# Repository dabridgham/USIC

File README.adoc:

= USIC - Unibus Storage and I/O Card

The USIC is a Unibus card with an FPGA and SD cards that emulates the old DEC disk
controllers and drives.

This repository is the KiCad project for the hardware, the USIC board
itself.  In addition there are separate projects for a QBUS version of
the board, the http://github.com/dabridgham/QSIC[QSIC], the
http://github.com/dabridgham/QSIC-Verilog[Verilog code] that runs on
the FPGAs, and the code that runs on the embedded soft processor (not
yet started).

A companion http://github.com/dabridgham/Indicator-Panel[indicator
panel] is also available for those who want the blinkenlights.

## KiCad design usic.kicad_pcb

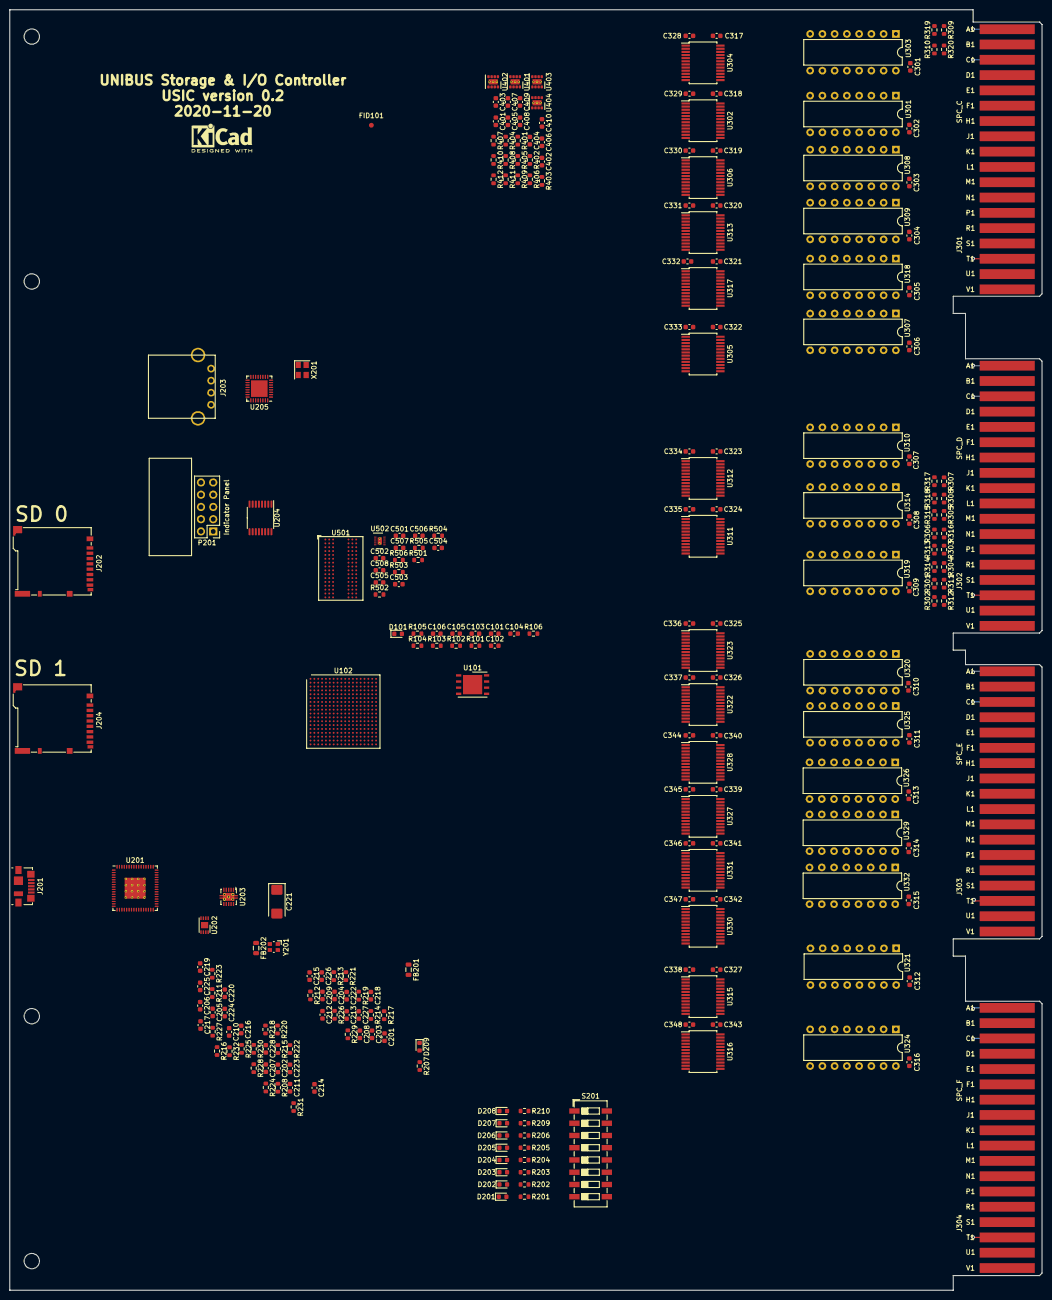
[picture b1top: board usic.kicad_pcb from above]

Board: 6 copper layers, 214.1 x 265.6 mm, 253 parts (0 on the bottom side), 359 nets.

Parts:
C101, C102, C103, C104, C106, C218, C226, C401, C405, C407, C409, C501, C502: 22µF 10V; C_0603_1608Metric
C105, C201, C202, C203, C204, C205, C206, C207, C209, C211, C212, C214, C217, C219, C220, C222, C223, C227, C301, C302, C303, C304, C305, C306, C307, C308, C309, C310, C311, C312, C313, C314, C315, C316, C317, C318, C319, C320, C321, C322, C323, C324, C325, C326, C327, C328, C329, C330, C331, C332, C333, C334, C335, C336, C337, C338, C339, C340, C341, C342, C343, C344, C345, C346, C347, C348, C508: 100nF; C_0603_1608Metric
C208, C210: 4.7µF 6.3V; C_0603_1608Metric
C213: 3.3µF 6.3V; C_0603_1608Metric
C215, C216: 8pF; C_0603_1608Metric
C221: 150µF; CP_EIA-6032-28_Kemet-C
C224, C225: 1µF; C_0603_1608Metric
C228: 10nF; C_0603_1608Metric
C402, C403, C404, C406, C408, C410, C503, C504, C505, C506: 10µF 10V; C_0603_1608Metric
C507: 220nF; C_0603_1608Metric
D101, D201, D202, D203, D204, D205, D206, D207, D208, D209: green; LED_0603_1608Metric
FB201, FB202: Ferrite_Bead_Small; L_0805_2012Metric
FID101: Fiducial; Fiducial_1mm_Mask2mm
Handle_101, Handle_102: Handle; DEC-Handle
Handle_Hole_101, Handle_Hole_102, Handle_Hole_103, Handle_Hole_104: MountingHole; mounting hole .125
J201: USB_B_Micro; USB_Micro-B_Molex_47346-0001
J202: SD 0; microSD_HC_Hirose_DM3BT-DSF-PEJS
J203: USB_A; USB-A-Amphenol-UE27
J204: SD 1; microSD_HC_Hirose_DM3BT-DSF-PEJS
J301: SPC_C; DEC_Edge_Fingers_single_height
J302: SPC_D; DEC_Edge_Fingers_single_height
J303: SPC_E; DEC_Edge_Fingers_single_height
J304: SPC_F; DEC_Edge_Fingers_single_height
LOGO101: KiCad Logo; KiCad-Logo2_5mm_SilkScreen
P201: Indicator Panel; Box_Header_2x05_P2.54mm
R101, R102, R105, R106: 4.7k; R_0603_1608Metric
R103: 2.4k; R_0603_1608Metric
R104, R201, R202, R203, R204, R205, R206, R209, R210, R214, R501: 240; R_0603_1608Metric
R207: 1k; R_0603_1608Metric
R208: 12k 1%; R_0603_1608Metric
R211, R212, R213, R504, R505, R506: 10k; R_0603_1608Metric
R215: 2.2k; R_0603_1608Metric
R216, R217: 100k; R_0603_1608Metric
R218, R226: 4.7; R_0603_1608Metric
R219, R220, R221, R222, R223, R227, R228, R229, R230, R231: 50k; R_0603_1608Metric
R224: 56.2k; R_0603_1608Metric
R225: 20k; R_0603_1608Metric
R232: 8.06k; R_0603_1608Metric
R301, R302, R303, R304, R305, R306, R307, R308, R309, R310: 330; R_0603_1608Metric
R311, R312, R313, R314, R315, R316, R317, R318, R319, R320: 680; R_0603_1608Metric
R401: 499k; R_0603_1608Metric
R402: 511k; R_0603_1608Metric
R403: 162k; R_0603_1608Metric
R404, R407, R410: 499k 1%; R_0603_1608Metric
R405: 200k 1%; R_0603_1608Metric
R406, R409, R412: 162k 1%; R_0603_1608Metric
R408: 143k 1%; R_0603_1608Metric
R411: 40.2 1%; R_0603_1608Metric
R502: 89 1%; R_0603_1608Metric
R503: 47k; R_0603_1608Metric
S201: Config; SW_DIP_SPSTx08_Slide_6.7x21.88mm_W6.73mm_P2.54mm_LowProfile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
U101: MT25Q-so8; DFN-8-1EP_6x5mm_P1.27mm_EP4x4mm
U102: XC7A75T-CSG324; Xilinx_CSG324
U201: FT2232HQ; QFN-64-1EP_9x9mm_P0.5mm_EP4.35x4.35mm_ThermalVias
U202: 93CxxC; DFN-8-1EP_3x2mm_P0.5mm_EP1.3x1.5mm
U203: TPS2561; VSON-10-1EP_3x3mm_P0.5mm_EP1.65x2.4mm_ThermalVias
U204: MAX3033E; TSSOP-16_4.4x5mm_P0.65mm
U205: USB3340; QFN-32-1EP_5x5mm_P0.5mm_EP3.45x3.45mm
U301, U303, U307, U308, U309, U310, U314, U318, U319, U320, U321, U324, U325, U326, U329, U332: DS8641-LR; DIP-16_W7.62mm
U302, U304, U305, U306, U311, U312, U313, U315, U316, U317, U322, U323, U327, U328, U330, U331: 74LVC7T245; SSOP-24_5.3x8.2mm_P0.65mm
U401, U402, U403, U404: TPS82085; Texas_SIL0008D_MicroSiP-8-1EP_2.8x3mm_P0.65mm_EP1.1x1.9mm_T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
U501: IS43TR16128B; BGA-96_9.0x13.0mm_Layout2x3x16_P0.8mm
U502: TPS51206; WSON-10-1EP_2x2mm_P0.4mm_EP0.9x1.5mm_ThermalVias
X201: ASE-24.000MHz; Oscillator_SMD_Abracon_ASE-4Pin_3.2x2.5mm
Y201: 12 MHz; Crystal_SMD_Abracon_ABM10-4Pin_2.5x2.0mm

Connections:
/1V0: C404.1, C409.1, R410.1, R411.1, U102.F8 (VCCINT), U102.F10 (VCCBRAM), U102.G7 (VCCINT), U102.G9 (VCCINT), U102.G11 (VCCBRAM), U102.H8 (VCCINT), U102.J7 (VCCINT), U102.J11 (VCCINT), U102.K8 (VCCINT), U102.L7 (VCCINT), U102.L11 (VCCINT), U102.M8 (VCCINT), U102.M10 (VCCINT), U102.N7 (VCCINT), U102.N9 (VCCINT), U102.N11 (VCCINT), U404.8 (Vout)
/1V5: C407.1, C501.1, C502.1, C503.1, C504.1, R407.1, R408.1, U102.A7 (VCCO_35), U102.C3 (VCCO_35), U102.D6 (VCCO_35), U102.F2 (VCCO_35), U102.G5 (VCCO_35), U102.J1 (VCCO_35), U403.8 (Vout), U501.A1 (VDDQ1), U501.A8 (VDDQ2), U501.B2 (VDD1), U501.C1 (VDDQ3), U501.C9 (VDDQ4), U501.D2 (VDDQ5), U501.D9 (VDD2), U501.E9 (VDDQ6), U501.F1 (VDDQ7), U501.G7 (VDD3), U501.H2 (VDDQ8), U501.H9 (VDDQ9), U501.K2 (VDD4), U501.K8 (VDD5), U501.N1 (VDD6), U501.N9 (VDD7), U501.R1 (VDD8), U501.R9 (VDD9), U502.1 (VDDQSNS)
/1V8: C403.1, C405.1, R404.1, R405.1, U102.F12 (VCCAUX), U102.H10 (VCCADC_0), U102.H12 (VCCAUX), U102.K12 (VCCAUX), U102.M12 (VCCAUX), U402.8 (Vout)
/3V3: C101.1, C102.2, C103.1, C104.2, C105.2, C106.2, C203.1, C205.1, C206.1, C211.1, C212.1, C214.2, C220.2, C222.1, C223.1, C228.1, C328.1, C329.1, C330.1, C331.1, C332.1, C333.1, C334.1, C335.1, C336.1, C337.1, C338.1, C344.1, C345.1, C346.1, C347.1, C348.1, C401.1, C505.1, C508.1, D209.2 (A), FB201.2, FB202.2, R101.1, R102.1, R103.1, R104.1, R105.1, R106.1, R201.1, R202.1, R203.1, R204.1, R205.1, R206.1, R207.2, R209.1, R210.1, R211.1, R212.1, R213.1, R218.2, R219.1, R220.1, R221.1, R222.1, R223.1, R226.2, R227.1, R228.1, R229.1, R230.1, R231.1, R401.1, R402.1, R505.2, R506.2, U101.8 (Vcc), U102.A17 (VCCO_15), U102.B10 (VCCO_16), U102.C13 (VCCO_15), U102.D16 (VCCO_15), U102.G15 (VCCO_15), U102.H18 (VCCO_15), U102.K4 (VCCO_34), U102.K14 (VCCO_15), U102.L17 (VCCO_14), U102.N3 (VCCO_34), U102.N13 (VCCO_14), U102.P6 (VCCO_34), U102.P8 (CFGBVS_0), U102.P12 (M0_0), U102.P16 (VCCO_14), U102.T2 (VCCO_34), U102.T12 (VCCO_14), U102.U5 (VCCO_34), U102.U15 (VCCO_14), U102.V8 (VCCO_34), U102.V18 (VCCO_14), U201.20 (VCCIO), U201.31 (VCCIO), U201.42 (VCCIO), U201.50 (VREGIN), U201.56 (VCCIO), U202.6 (ORG), U202.8 (VCC), U204.4 (EN12), U204.12 (EN34), U204.16 (VDD), U205.8 (REFSEL[0]), U205.11 (REFSEL[1]), U205.14 (REFSEL[2]), U205.21 (VBAT), U205.32 (VDDIO), U302.1 (VCCa), U302.2 (A->B), U304.1 (VCCa), U304.2 (A->B), U305.1 (VCCa), U306.1 (VCCa), U311.1 (VCCa), U311.2 (A->B), U312.1 (VCCa), U313.1 (VCCa), U313.2 (A->B), U315.1 (VCCa), U315.2 (A->B), U316.1 (VCCa), U317.1 (VCCa), U322.1 (VCCa), U322.2 (A->B), U323.1 (VCCa), U327.1 (VCCa), U327.2 (A->B), U328.1 (VCCa), U330.1 (VCCa), U330.2 (A->B), U331.1 (VCCa), U401.8 (Vout), U502.2 (VLDOIN), U502.10 (VDD), X201.4 (Vdd)
/5V0: C217.1, C301.1, C302.1, C303.1, C304.1, C305.1, C306.1, C307.1, C308.1, C309.1, C310.1, C311.1, C312.1, C313.1, C314.1, C315.1, C316.1, C317.1, C318.1, C319.1, C320.1, C321.1, C322.1, C323.1, C324.1, C325.1, C326.1, C327.1, C339.1, C340.1, C341.1, C342.1, C343.1, C402.1, C406.1, C408.1, C410.1, J301.A2 (+5V), J302.A2 (+5V), J303.A2 (+5V), J304.A2 (+5V), R216.1, R217.1, R301.1, R302.1, R303.1, R304.1, R305.1, R306.1, R307.1, R308.1, R309.1, R310.1, U203.2 (IN), U203.3 (IN), U301.16 (VCC), U302.23 (VCCb), U302.24 (VCCb), U303.16 (VCC), U304.23 (VCCb), U304.24 (VCCb), U305.23 (VCCb), U305.24 (VCCb), U306.23 (VCCb), U306.24 (VCCb), U307.16 (VCC), U308.16 (VCC), U309.16 (VCC), U310.16 (VCC), U311.23 (VCCb), U311.24 (VCCb), U312.23 (VCCb), U312.24 (VCCb), U313.23 (VCCb), U313.24 (VCCb), U314.16 (VCC), U315.23 (VCCb), U315.24 (VCCb), U316.23 (VCCb), U316.24 (VCCb), U317.23 (VCCb), U317.24 (VCCb), U318.16 (VCC), U319.16 (VCC), U320.16 (VCC), U321.16 (VCC), U322.23 (VCCb), U322.24 (VCCb), U323.23 (VCCb), U323.24 (VCCb), U324.16 (VCC), U325.16 (VCC), U326.16 (VCC), U327.23 (VCCb), U327.24 (VCCb), U328.23 (VCCb), U328.24 (VCCb), U329.16 (VCC), U330.23 (VCCb), U330.24 (VCCb), U331.23 (VCCb), U331.24 (VCCb), U332.16 (VCC), U401.1 (En), U401.3 (Vin), U401.4 (Vin), U402.1 (En), U402.3 (Vin), U402.4 (Vin), U403.1 (En), U403.3 (Vin), U403.4 (Vin), U404.1 (En), U404.3 (Vin), U404.4 (Vin)
/CLK_INPUT: U102.D15 (IO_L12P_T1_MRCC_15), U102.H16 (IO_L13P_T2_MRCC_15), U102.N5 (IO_L13P_T2_MRCC_34), U102.P15 (IO_L13P_T2_MRCC_14), U102.P17 (IO_L12P_T1_MRCC_14), U102.T5 (IO_L12P_T1_MRCC_34)
/I/O/D+: J201.3 (D+), U201.8 (D+)
/I/O/D-: J201.2 (D-), U201.7 (D-)
/I/O/IPblank_N: P201.7, U204.5 (O2-)
/I/O/IPblank_P: P201.6, U204.6 (O2+)
/I/O/IPclk_N: P201.10, U204.3 (O1-)
/I/O/IPclk_P: P201.9, U204.2 (O1+)
/I/O/IPdata_N: P201.2, U204.13 (O4-)
/I/O/IPdata_P: P201.1, U204.14 (O4+)
/I/O/IPlatch_N: P201.5, U204.11 (O3-)
/I/O/IPlatch_P: P201.4, U204.10 (O3+)
/LED_0: D201.1 (K), U102.V9 (IO_L21N_T3_DQS_34)
/LED_1: D202.1 (K), U102.U7 (IO_L22P_T3_34)
/LED_2: D203.1 (K), U102.U6 (IO_L22N_T3_34)
/LED_3: D204.1 (K), U102.R7 (IO_L23P_T3_34)
/LED_4: D205.1 (K), U102.T6 (IO_L23N_T3_34)
/LED_5: D206.1 (K), U102.R8 (IO_L24P_T3_34)
/LED_6: D207.1 (K), U102.T8 (IO_L24N_T3_34)
/LED_7: D208.1 (K), U102.U8 (IO_25_34)
/Memory/A0: U102.C5 (IO_L1N_T0_AD4N_35), U501.N3 (A0)
/Memory/A1: U102.B6 (IO_L2N_T0_AD12N_35), U501.P7 (A1)
/Memory/A2: U102.C7 (IO_L4N_T0_35), U501.P3 (A2)
/Memory/A3: U102.D5 (IO_L11P_T1_SRCC_35), U501.N2 (A3)
/Memory/A4: U102.A3 (IO_L8N_T1_AD14N_35), U501.P8 (A4)
/Memory/A5: U102.E7 (IO_L6P_T0_35), U501.P2 (A5)
/Memory/A6: U102.A4 (IO_L8P_T1_AD14P_35), U501.R8 (A6)
/Memory/A7: U102.C6 (IO_L1P_T0_AD4P_35), U501.R2 (A7)
/Memory/A8: U102.A6 (IO_L3P_T0_DQS_AD5P_35), U501.T8 (A8)
/Memory/A9: U102.D8 (IO_L4P_T0_35), U501.R3 (A9)
/Memory/A10: U102.B2 (IO_L10N_T1_AD15N_35), U501.L7 (A10/AP)
/Memory/A11: U102.A5 (IO_L3N_T0_DQS_AD5N_35), U501.R7 (A11)
/Memory/A12: U102.B3 (IO_L10P_T1_AD15P_35), U501.N7 (A12/BC#)
/Memory/A13: U102.B7 (IO_L2P_T0_AD12P_35), U501.T3 (A13)
/Memory/BA0: U102.E5 (IO_L5N_T0_AD13N_35), U501.M2 (BA0)
/Memory/BA1: U102.A1 (IO_L9N_T1_DQS_AD7N_35), U501.N8 (BA1)
/Memory/BA2: U102.E6 (IO_L5P_T0_AD13P_35), U501.M3 (BA2)
/Memory/CAS#: U102.D3 (IO_L12N_T1_MRCC_35), U501.K3 (CAS#)
/Memory/CK: R502.2, U102.C4 (IO_L7P_T1_AD6P_35), U501.J7 (CK)
/Memory/CK#: R502.1, U102.B4 (IO_L7N_T1_AD6N_35), U501.K7 (CK#)
/Memory/CKE: U102.B1 (IO_L9P_T1_DQS_AD7P_35), U501.K9 (CKE)
/Memory/DML: U102.G1 (IO_L17N_T2_35), U501.E7 (DML)
/Memory/DMU: U102.G6 (IO_L19P_T3_35), U501.D3 (DMU)
/Memory/DQL0: U102.H1 (IO_L17P_T2_35), U501.E3 (DQL0)
/Memory/DQL1: U102.F1 (IO_L18P_T2_35), U501.F7 (DQL1)
/Memory/DQL2: U102.E2 (IO_L14P_T2_SRCC_35), U501.F2 (DQL2)
/Memory/DQL3: U102.E1 (IO_L18N_T2_35), U501.F8 (DQL3)
/Memory/DQL4: U102.F4 (IO_L13P_T2_MRCC_35), U501.H3 (DQL4)
/Memory/DQL5: U102.C1 (IO_L16N_T2_35), U501.H8 (DQL5)
/Memory/DQL6: U102.F3 (IO_L13N_T2_MRCC_35), U501.G2 (DQL6)
/Memory/DQL7: U102.D2 (IO_L14N_T2_SRCC_35), U501.H7 (DQL7)
/Memory/DQSL: U102.H2 (IO_L15P_T2_DQS_35), U501.F3 (DQSL)
/Memory/DQSL#: U102.G2 (IO_L15N_T2_DQS_35), U501.G3 (DQSL#)
/Memory/DQSU: U102.J4 (IO_L21P_T3_DQS_35), U501.C7 (DQSU)
/Memory/DQSU#: U102.H4 (IO_L21N_T3_DQS_35), U501.B7 (DQSU#)
/Memory/DQU0: U102.G4 (IO_L20P_T3_35), U501.D7 (DQU0)
/Memory/DQU1: U102.H5 (IO_L24N_T3_35), U501.C3 (DQU1)
/Memory/DQU2: U102.G3 (IO_L20N_T3_35), U501.C8 (DQU2)
/Memory/DQU3: U102.H6 (IO_L24P_T3_35), U501.C2 (DQU3)
/Memory/DQU4: U102.J2 (IO_L22N_T3_35), U501.A7 (DQU4)
/Memory/DQU5: U102.J3 (IO_L22P_T3_35), U501.A2 (DQU5)
/Memory/DQU6: U102.K1 (IO_L23N_T3_35), U501.B8 (DQU6)
/Memory/DQU7: U102.K2 (IO_L23P_T3_35), U501.A3 (DQU7)
/Memory/ODT: U102.F5 (IO_0_35), U501.K1 (ODT)
/Memory/RAS#: U102.E3 (IO_L12P_T1_MRCC_35), U501.J3 (RAS#)
/Memory/RESET#: R503.1, U102.J5 (IO_25_35), U501.T2 (RESET#)
/Memory/VREF15: C507.1, U102.D7 (IO_L6N_T0_VREF_35), U102.F6 (IO_L19N_T3_VREF_35), U501.H1 (VREFDQ), U501.M8 (VREFCA), U502.6 (VTTREF)
/Memory/WE#: U102.D4 (IO_L11N_T1_SRCC_35), U501.L3 (WE#)
/PROG_B: R106.2, U102.P9 (PROGRAM_B_0)
/RXD: U102.B9 (IO_L11N_T1_SRCC_16), U201.39 (BDBUS1)
/SW_0: S201.8, U102.U1 (IO_L7P_T1_34)
/SW_1: S201.7, U102.V1 (IO_L7N_T1_34)
/SW_2: S201.6, U102.U4 (IO_L8P_T1_34)
/SW_3: S201.5, U102.U3 (IO_L8N_T1_34)
/SW_4: S201.4, U102.U2 (IO_L9P_T1_DQS_34)
/SW_5: S201.3, U102.V2 (IO_L9N_T1_DQS_34)
/SW_6: S201.2, U102.V5 (IO_L10P_T1_34)
/SW_7: S201.1, U102.V4 (IO_L10N_T1_34)
/TCK: U102.E10 (TCK_0), U201.16 (ADBUS0)
/TDI: U102.E11 (TDI_0), U201.17 (ADBUS1)
/TDO: U102.E13 (TDO_0), U201.18 (ADBUS2)
/TMS: U102.E12 (TMS_0), U201.19 (ADBUS3)
/TXD: U102.C9 (IO_L11P_T1_SRCC_16), U201.38 (BDBUS0)
/Unibus/A0: J303.H2 (A00), U325.1 (bus3)
/Unibus/A1: J303.H1 (A01), U325.15 (bus1)
/Unibus/A2: J303.F1 (A02), U325.12 (bus2)
/Unibus/A3: J303.V2 (A03), U332.15 (bus1)
/Unibus/A4: J303.U2 (A04), U332.1 (bus3)
/Unibus/A5: J303.V1 (A05), U332.12 (bus2)
/Unibus/A6: J303.U1 (A06), U332.4 (bus4)
/Unibus/A7: J303.P2 (A07), U329.1 (bus3)
/Unibus/A8: J303.N2 (A08), U329.4 (bus4)
/Unibus/A9: J303.R1 (A09), U329.15 (bus1)
/Unibus/A10: J303.P1 (A10), U329.12 (bus2)
/Unibus/A11: J303.L1 (A11), U326.15 (bus1)
/Unibus/A12: J303.C1 (A12), U320.1 (bus3)
/Unibus/A13: J303.K2 (A13), U326.1 (bus3)
/Unibus/A14: J303.K1 (A14), U326.4 (bus4)
/Unibus/A15: J303.D2 (A15), U320.12 (bus2)
/Unibus/A16: J303.E2 (A16), U320.4 (bus4)
/Unibus/A17: J303.D1 (A17), U320.15 (bus1)
/Unibus/AC_LO: J301.V1 (AC_LO), U305.8 (A5), U307.1 (bus3)
/Unibus/BBSY: J304.D1 (BBSY), U324.1 (bus3)
/Unibus/BG4_in: J302.S2 (BG4_in), R301.2, R311.1, U312.9 (A6), U319.15 (bus1)
/Unibus/BG4_out: J302.T2 (BG4_out), R302.2, R312.1, U311.8 (A5), U319.12 (bus2)
/Unibus/BG5_in: J302.P2 (BG5_in), R303.2, R313.1, U312.10 (A7), U319.4 (bus4)
/Unibus/BG5_out: J302.R2 (BG5_out), R304.2, R314.1, U311.9 (A6), U319.1 (bus3)
/Unibus/BG6_in: J302.M2 (BG6_in), R305.2, R315.1, U312.8 (A5), U314.15 (bus1)
/Unibus/BG6_out: J302.N2 (BG6_out), R306.2, R316.1, U311.6 (A3), U314.12 (bus2)
/Unibus/BG7_in: J302.K2 (BG7_in), R307.2, R317.1, U310.12 (bus2), U312.6 (A3)
/Unibus/BG7_out: J302.L2 (BG7_out), R308.2, R318.1, U311.7 (A4), U314.1 (bus3)
/Unibus/BR4: J302.H2 (BR4), U310.15 (bus1)
/Unibus/BR5: J302.F2 (BR5), U310.1 (bus3)
/Unibus/BR6: J302.E2 (BR6), U310.4 (bus4)
/Unibus/BR7: J302.D2 (BR7), U307.12 (bus2)
/Unibus/C0: J303.J2 (C0), U321.4 (bus4)
/Unibus/C1: J303.F2 (C1), U321.1 (bus3)
/Unibus/D0: J301.S2 (D00), U318.15 (bus1)
/Unibus/D1: J301.R2 (D01), U309.4 (bus4)
/Unibus/D2: J301.U2 (D02), U318.1 (bus3)
/Unibus/D3: J301.T2 (D03), U318.12 (bus2)
/Unibus/D4: J301.N2 (D04), U309.12 (bus2)
/Unibus/D5: J301.P2 (D05), U309.1 (bus3)
/Unibus/D6: J301.V2 (D06), U318.4 (bus4)
/Unibus/D7: J301.M2 (D07), U309.15 (bus1)
/Unibus/D8: J301.L2 (D08), U308.4 (bus4)
/Unibus/D9: J301.K2 (D09), U308.1 (bus3)
/Unibus/D10: J301.J2 (D10), U308.12 (bus2)
/Unibus/D11: J301.H1 (D11), U308.15 (bus1)
/Unibus/D12: J301.H2 (D12), U301.4 (bus4)
/Unibus/D13: J301.F2 (D13), U301.1 (bus3)
/Unibus/D14: J301.E2 (D14), U301.12 (bus2)
/Unibus/D15: J301.D2 (D15), U301.15 (bus1)
/Unibus/DC_LO: J301.N1 (DC_LO), U305.7 (A4), U307.4 (bus4)
/Unibus/INIT: J302.L1 (INIT), U314.4 (bus4)
/Unibus/INTR: J304.M1 (INTR), U324.15 (bus1)
/Unibus/MSYN: J303.E1 (MSYN), U321.15 (bus1)
/Unibus/NPG_in: J301.A1 (NPG_in), R309.2, R319.1, U303.1 (bus3), U305.4 (A1)
/Unibus/NPG_out: J301.B1 (NPG_out), R310.2, R320.1, U303.4 (bus4), U304.3 (A0)
/Unibus/NPR: J304.J1 (NPR), U324.4 (bus4)
/Unibus/PA: J301.C1 (PA), U303.15 (bus1)
/Unibus/PB: J301.S1 (PB), U307.15 (bus1)
/Unibus/SACK: J304.T2 (SACK), U324.12 (bus2)
/Unibus/SSYN: J303.J1 (SSYN), U321.12 (bus2)
/Unibus/~RxA: U323.22 (~OE), U328.22 (~OE), U331.22 (~OE)
/Unibus/~RxD: U306.22 (~OE), U317.22 (~OE)
/Unibus/~TxA_5: U311.14 (B7), U320.7 (disB), U325.7 (disB), U326.7 (disB), U329.7 (disB), U332.7 (disB)
/Unibus/~TxD_5: U301.7 (disB), U304.14 (B7), U308.7 (disB), U309.7 (disB), U318.7 (disB)
/ip_blank: U102.V7 (IO_L20P_T3_34), U204.7 (I2)
/ip_clk: U102.R5 (IO_L19N_T3_VREF_34), U204.1 (I1)
/ip_data: U102.U9 (IO_L21P_T3_DQS_34), U204.15 (I4)
/ip_latch: U102.V6 (IO_L20N_T3_34), U204.9 (I3)
/sd0_clk: J202.5 (CLK), U102.P2 (IO_L15P_T2_DQS_34)
/sd0_cmd: J202.3 (CMD), R221.2, U102.P3 (IO_L14N_T2_SRCC_34)
/sd0_dat0: J202.7 (DAT0), R220.2, U102.R3 (IO_L11P_T1_SRCC_34)
/sd0_dat1: J202.8 (DAT1), R219.2, U102.T3 (IO_L11N_T1_SRCC_34)
/sd0_dat2: J202.1 (DAT2), R223.2, U102.P5 (IO_L13N_T2_MRCC_34)
/sd0_dat3: J202.2 (DAT3/CD), R222.2, U102.P4 (IO_L14P_T2_SRCC_34)
/sd0_det: J202.9 (DET_B), U102.R2 (IO_L15N_T2_DQS_34)
/sd1_clk: J204.5 (CLK), U102.N6 (IO_L18N_T2_34)
/sd1_cmd: J204.3 (CMD), R229.2, U102.M6 (IO_L18P_T2_34)
/sd1_dat0: J204.7 (DAT0), R228.2, U102.M4 (IO_L16P_T2_34)
/sd1_dat1: J204.8 (DAT1), R227.2, U102.N4 (IO_L16N_T2_34)
/sd1_dat2: J204.1 (DAT2), R231.2, U102.R1 (IO_L17P_T2_34)
/sd1_dat3: J204.2 (DAT3/CD), R230.2, U102.T1 (IO_L17N_T2_34)
/sd1_det: J204.9 (DET_B), U102.R6 (IO_L19P_T3_34)
/usb0_clk60: U102.L6 (IO_L6P_T0_34), U205.1 (CLKOUT)
/usb0_d0: U102.K6 (IO_0_34), U205.3 (DATA0)
/usb0_d1: U102.L1 (IO_L1P_T0_34), U205.4 (DATA1)
/usb0_d2: U102.M1 (IO_L1N_T0_34), U205.5 (DATA2)
/usb0_d3: U102.K3 (IO_L2P_T0_34), U205.6 (DATA3)
/usb0_d4: U102.L3 (IO_L2N_T0_34), U205.7 (DATA4)
/usb0_d5: U102.N2 (IO_L3P_T0_DQS_34), U205.9 (DATA5)
/usb0_d6: U102.N1 (IO_L3N_T0_DQS_34), U205.10 (DATA6)
/usb0_d7: U102.M3 (IO_L4P_T0_34), U205.13 (DATA7)
/usb0_dir: U102.K5 (IO_L5P_T0_34), U205.31 (DIR)
/usb0_nxt: U102.M2 (IO_L4N_T0_34), U205.2 (NXT)
/usb0_reset: U102.L5 (IO_L6N_T0_VREF_34), U205.27 (RESET)
/usp0_stp: U102.L4 (IO_L5N_T0_34), U205.29 (STP)
/~CTS: U102.A8 (IO_L12N_T1_MRCC_16), U201.41 (BDBUS3)
/~DCD: U102.A10 (IO_L14P_T2_SRCC_16), U201.45 (BDBUS6)
/~DSR: U102.C10 (IO_L13N_T2_MRCC_16), U201.44 (BDBUS5)
/~DTR: U102.C11 (IO_L13P_T2_MRCC_16), U201.43 (BDBUS4)
/~RI: U102.D10 (IO_L19N_T3_VREF_16), U201.46 (BDBUS7)
/~RTS: U102.D9 (IO_L6N_T0_VREF_16), U201.40 (BDBUS2)
GND: C101.2, C102.1, C103.2, C104.1, C105.1, C106.1, C201.2, C202.2, C203.2, C204.2, C205.2, C206.2, C207.2, C208.2, C209.2, C210.2, C211.2, C212.2, C213.2, C214.1, C215.1, C216.1, C217.2, C218.2, C219.2, C220.1, C221.2, C222.2, C223.2, C224.2, C225.2, C226.2, C227.2, C228.2, C301.2, C302.2, C303.2, C304.2, C305.2, C306.2, C307.2, C308.2, C309.2, C310.2, C311.2, C312.2, C313.2, C314.2, C315.2, C316.2, C317.2, C318.2, C319.2, C320.2, C321.2, C322.2, C323.2, C324.2, C325.2, C326.2, C327.2, C328.2, C329.2, C330.2, C331.2, C332.2, C333.2, C334.2, C335.2, C336.2, C337.2, C338.2, C339.2, C340.2, C341.2, C342.2, C343.2, C344.2, C345.2, C346.2, C347.2, C348.2, C401.2, C402.2, C403.2, C404.2, C405.2, C406.2, C407.2, C408.2, C409.2, C410.2, C501.2, C502.2, C503.2, C504.2, C505.2, C506.2, C507.2, C508.2, J201.5 (GND), J201.6 (Shield), J202.6 (VSS), J202.10 (DET_A), J202.11 (SHIELD), J203.4 (GND), J203.5 (Shield), J204.6 (VSS), J204.10 (DET_A), J204.11 (SHIELD), J301.C2 (GND), J301.T1 (GND), J302.C2 (GND), J302.T1 (GND), J303.C2 (GND), J303.T1 (GND), J304.C2 (GND), J304.T1 (GND), P201.3, P201.8, R208.2, R224.2, R232.2, R311.2, R312.2, R313.2, R314.2, R315.2, R316.2, R317.2, R318.2, R319.2, R320.2, R403.2, R406.2, R409.2, R412.2, R501.2, R503.2, R504.1, S201.9, S201.10, S201.11, S201.12, S201.13, S201.14, S201.15, S201.16, U101.4 (Vss), U101.9 (EP), U102.A2 (GND), U102.A12 (GND), U102.B5 (GND), U102.B15 (GND), U102.C8 (GND), U102.C18 (GND), U102.D1 (GND), U102.D11 (GND), U102.E4 (GND), U102.E8 (VCCBATT_0), U102.E14 (GND), U102.F7 (GND), U102.F9 (GND), U102.F11 (GND), U102.F17 (GND), U102.G8 (GND), U102.G10 (GND), U102.G12 (GND), U102.H3 (GND), U102.H7 (GND), U102.H9 (GNDADC_0), U102.H11 (GND), U102.H13 (GND), U102.J6 (GND), U102.J8 (GND), U102.J9 (VREFN_0), U102.J12 (GND), U102.J16 (GND), U102.K7 (GND), U102.K10 (VREFP_0), U102.K11 (GND), U102.L2 (GND), U102.L8 (GND), U102.L12 (GND), U102.M5 (GND), U102.M7 (GND), U102.M9 (GND), U102.M11 (GND), U102.M15 (GND), U102.N8 (GND), U102.N10 (GND), U102.N12 (GND), U102.N18 (GND), U102.P1 (GND), U102.P11 (M2_0), U102.P13 (M1_0), U102.R4 (GND), U102.R14 (GND), U102.T7 (GND), U102.T17 (GND), U102.U10 (GND), U102.V3 (GND), U102.V13 (GND), U201.1 (GND), U201.5 (GND), U201.10 (AGND), U201.11 (GND), U201.13 (TEST), U201.15 (GND), U201.25 (GND), U201.35 (GND), U201.47 (GND), U201.51 (GND), U201.65 (EP), U202.5 (GND), U203.1 (GND), U203.4 (EN1), U203.11 (PAD), U204.8 (GND), U205.33 (GND), U301.8 (GND), U301.9 (disA), U302.11 (GND), U302.12 (GND), U302.13 (GND), U302.22 (~OE), U303.7 (disB), U303.8 (GND), U303.9 (disA), U304.11 (GND), U304.12 (GND), U304.13 (GND), U304.22 (~OE), U305.2 (A->B), U305.11 (GND), U305.12 (GND), U305.13 (GND), U305.22 (~OE), U306.2 (A->B), U306.11 (GND), U306.12 (GND), U306.13 (GND), U307.7 (disB), U307.8 (GND), U307.9 (disA), U308.8 (GND), U308.9 (disA), U309.8 (GND), U309.9 (disA), U310.7 (disB), U310.8 (GND), U310.9 (disA), U310.11 (in2), U311.11 (GND), U311.12 (GND), U311.13 (GND), U311.22 (~OE), U312.2 (A->B), U312.11 (GND), U312.12 (GND), U312.13 (GND), U312.22 (~OE), U313.11 (GND), U313.12 (GND), U313.13 (GND), U313.22 (~OE), U314.7 (disB), U314.8 (GND), U314.9 (disA), U315.11 (GND), U315.12 (GND), U315.13 (GND), U315.22 (~OE), U316.2 (A->B), U316.11 (GND), U316.12 (GND), U316.13 (GND), U316.22 (~OE), U317.2 (A->B), U317.11 (GND), U317.12 (GND), U317.13 (GND), U318.8 (GND), U318.9 (disA), U319.7 (disB), U319.8 (GND), U319.9 (disA), U320.8 (GND), U320.9 (disA), U321.7 (disB), U321.8 (GND), U321.9 (disA), U322.11 (GND), U322.12 (GND), U322.13 (GND), U322.22 (~OE), U323.2 (A->B), U323.11 (GND), U323.12 (GND), U323.13 (GND), U324.7 (disB), U324.8 (GND), U324.9 (disA), U325.8 (GND), U325.9 (disA), U326.8 (GND), U326.9 (disA), U327.11 (GND), U327.12 (GND), U327.13 (GND), U327.22 (~OE), U328.2 (A->B), U328.11 (GND), U328.12 (GND), U328.13 (GND), U329.8 (GND), U329.9 (disA), U330.11 (GND), U330.12 (GND), U330.13 (GND), U330.22 (~OE), U331.2 (A->B), U331.11 (GND), U331.12 (GND), U331.13 (GND), U332.8 (GND), U332.9 (disA), U401.5 (GND), U401.6 (GND), U401.9 (GND), U402.5 (GND), U402.6 (GND), U402.9 (GND), U403.5 (GND), U403.6 (GND), U403.9 (GND), U404.5 (GND), U404.6 (GND), U404.9 (GND), U501.A9 (VSS1), U501.B1 (VSSQ1), U501.B3 (VSS2), U501.B9 (VSSQ2), U501.D1 (VSSQ3), U501.D8 (VSSQ4), U501.E1 (VSS3), U501.E2 (VSSQ5), U501.E8 (VSSQ6), U501.F9 (VSSQ7), U501.G1 (VSSQ8), U501.G8 (VSS4), U501.G9 (VSSQ9), U501.J2 (VSS5), U501.J8 (VSS6), U501.M1 (VSS7), U501.M9 (VSS8), U501.P1 (VSS9), U501.P9 (VSS10), U501.T1 (VSS11), U501.T9 (VSS12), U502.4 (PGND), U502.8 (GND), U502.11 (PowerPad), X201.2 (GND)
unnamed: C201.1, C202.1, C204.1, C213.1, U201.12 (VCORE), U201.37 (VCORE), U201.49 (VREGOUT), U201.64 (VCORE)
unnamed: C207.1, C208.1, FB202.1, U201.4 (VPHY)
unnamed: C209.1, C210.1, FB201.1, U201.9 (VPLL)
unnamed: C215.2, U201.2 (OSCI), Y201.3
unnamed: C216.2, U201.3 (OSCO), Y201.1
unnamed: C218.1, C219.1, J202.4 (VDD), R218.1
unnamed: C221.1, J203.1 (VBUS), R225.2, U203.8 (OUT2)
unnamed: C224.1, U205.20 (VDD33), U205.23 (ID)
unnamed: C225.1, U205.28 (VDD18)
unnamed: C226.1, C227.1, J204.4 (VDD), R226.1
unnamed: C506.1, R504.2, U502.3 (VTT), U502.5 (VTTSNS)
unnamed: D101.1 (K), U102.P10 (DONE_0)
unnamed: D101.2 (A), R104.2
unnamed: D201.2 (A), R201.2
unnamed: D202.2 (A), R202.2
unnamed: D203.2 (A), R203.2
unnamed: D204.2 (A), R204.2
unnamed: D205.2 (A), R205.2
unnamed: D206.2 (A), R206.2
unnamed: D207.2 (A), R209.2
unnamed: D208.2 (A), R210.2
unnamed: D209.1 (K), R214.1
unnamed: J203.2 (D-), U205.19 (DM)
unnamed: J203.3 (D+), U205.18 (DP)
unnamed: R101.2, U101.3 (~W/DQ2), U102.L14 (IO_L2P_T0_D02_14)
unnamed: R102.2, U101.7 (~HOLD/DQ3), U102.M14 (IO_L2N_T0_D03_14)
unnamed: R103.2, U101.1 (~S), U102.L13 (IO_L6P_T0_FCS_B_14)
unnamed: R105.2, U102.P7 (INIT_B_0)
unnamed: R207.1, U201.14 (~RESET)
unnamed: R208.1, U201.6 (REF)
unnamed: R211.2, U201.63 (EECS), U202.1 (CS)
unnamed: R212.2, U201.62 (EECLK), U202.2 (SCLK)
unnamed: R213.2, R215.1, U201.61 (EEDATA), U202.3 (DI)
unnamed: R214.2, U201.54 (BCBUS3), U201.55 (BCBUS4)
unnamed: R215.2, U202.4 (DO)
unnamed: R216.2, U203.10 (~FAULT1)
unnamed: R217.2, U203.6 (~FAULT2)
unnamed: R224.1, U203.7 (ILM)
unnamed: R225.1, U205.22 (VBUS)
unnamed: R232.1, U205.24 (RBIAS)
unnamed: R401.2, U401.2 (PG)
unnamed: R402.2, R403.1, U401.7 (FB)
unnamed: R404.2, U402.2 (PG)
unnamed: R405.2, R406.1, U402.7 (FB)
unnamed: R407.2, U403.2 (PG)
unnamed: R408.2, R409.1, U403.7 (FB)
unnamed: R410.2, U404.2 (PG)
unnamed: R411.2, R412.1, U404.7 (FB)
unnamed: R501.1, U501.L8 (ZQ)
unnamed: R505.1, U502.9 (S5)
unnamed: R506.1, U502.7 (S3)
unnamed: U101.2 (DQ1), U102.K18 (IO_L1N_T0_D01_DIN_14)
unnamed: U101.5 (DQ0), U102.K17 (IO_L1P_T0_D00_MOSI_14)
unnamed: U101.6 (C), U102.E9 (CCLK_0)
unnamed: U203.5 (EN2), U205.17 (CPEN)
unnamed: U205.26 (XI/REFCLK), X201.3 (OUT)
unnamed: U301.2 (in3), U302.19 (B2)
unnamed: U301.3 (out3), U306.19 (B2)
unnamed: U301.5 (in4), U302.18 (B3)
unnamed: U301.6 (out4), U306.18 (B3)
unnamed: U301.10 (out2), U306.20 (B1)
unnamed: U301.11 (in2), U302.20 (B1)
unnamed: U301.13 (out1), U306.21 (B0)
unnamed: U301.14 (in1), U302.21 (B0)
unnamed: U302.14 (B7), U308.5 (in4)
unnamed: U302.15 (B6), U308.2 (in3)
unnamed: U302.16 (B5), U308.11 (in2)
unnamed: U302.17 (B4), U308.14 (in1)
unnamed: U303.3 (out3), U305.20 (B1)
unnamed: U303.5 (in4), U304.21 (B0)
unnamed: U303.13 (out1), U305.19 (B2)
unnamed: U303.14 (in1), U304.19 (B2)
unnamed: U304.15 (B6), U307.2 (in3)
unnamed: U304.16 (B5), U307.14 (in1)
unnamed: U305.14 (B7), U307.10 (out2)
unnamed: U305.15 (B6), U307.13 (out1)
unnamed: U305.16 (B5), U307.3 (out3)
unnamed: U305.17 (B4), U307.6 (out4)
unnamed: U306.14 (B7), U308.6 (out4)
unnamed: U306.15 (B6), U308.3 (out3)
unnamed: U306.16 (B5), U308.10 (out2)
unnamed: U306.17 (B4), U308.13 (out1)
unnamed: U309.2 (in3), U313.19 (B2)
unnamed: U309.3 (out3), U317.19 (B2)
unnamed: U309.5 (in4), U313.18 (B3)
unnamed: U309.6 (out4), U317.18 (B3)
unnamed: U309.10 (out2), U317.20 (B1)
unnamed: U309.11 (in2), U313.20 (B1)
unnamed: U309.13 (out1), U317.21 (B0)
unnamed: U309.14 (in1), U313.21 (B0)
unnamed: U310.2 (in3), U311.20 (B1)
unnamed: U310.3 (out3), U312.20 (B1)
unnamed: U310.5 (in4), U311.21 (B0)
unnamed: U310.6 (out4), U312.21 (B0)
unnamed: U310.10 (out2), U312.18 (B3)
unnamed: U310.13 (out1), U312.19 (B2)
unnamed: U310.14 (in1), U311.19 (B2)
unnamed: U311.15 (B6), U319.2 (in3)
unnamed: U311.16 (B5), U319.11 (in2)
unnamed: U311.17 (B4), U314.2 (in3)
unnamed: U311.18 (B3), U314.11 (in2)
unnamed: U312.14 (B7), U319.6 (out4)
unnamed: U312.15 (B6), U319.13 (out1)
unnamed: U312.16 (B5), U314.13 (out1)
unnamed: U312.17 (B4), U314.6 (out4)
unnamed: U313.14 (B7), U318.5 (in4)
unnamed: U313.15 (B6), U318.2 (in3)
unnamed: U313.16 (B5), U318.11 (in2)
unnamed: U313.17 (B4), U318.14 (in1)
unnamed: U315.14 (B7), U324.5 (in4)
unnamed: U315.15 (B6), U324.2 (in3)
unnamed: U315.16 (B5), U324.11 (in2)
unnamed: U315.17 (B4), U324.14 (in1)
unnamed: U315.18 (B3), U321.5 (in4)
unnamed: U315.19 (B2), U321.2 (in3)
unnamed: U315.20 (B1), U321.11 (in2)
unnamed: U315.21 (B0), U321.14 (in1)
unnamed: U316.14 (B7), U324.6 (out4)
unnamed: U316.15 (B6), U324.3 (out3)
unnamed: U316.16 (B5), U324.10 (out2)
unnamed: U316.17 (B4), U324.13 (out1)
unnamed: U316.18 (B3), U321.3 (out3)
unnamed: U316.19 (B2), U321.6 (out4)
unnamed: U316.20 (B1), U321.10 (out2)
unnamed: U316.21 (B0), U321.13 (out1)
unnamed: U317.14 (B7), U318.6 (out4)
unnamed: U317.15 (B6), U318.3 (out3)
unnamed: U317.16 (B5), U318.10 (out2)
unnamed: U317.17 (B4), U318.13 (out1)
unnamed: U320.2 (in3), U322.19 (B2)
unnamed: U320.3 (out3), U323.19 (B2)
unnamed: U320.5 (in4), U322.18 (B3)
unnamed: U320.6 (out4), U323.18 (B3)
unnamed: U320.10 (out2), U323.20 (B1)
unnamed: U320.11 (in2), U322.20 (B1)
unnamed: U320.13 (out1), U323.21 (B0)
unnamed: U320.14 (in1), U322.21 (B0)
unnamed: U322.14 (B7), U325.5 (in4)
unnamed: U322.15 (B6), U325.2 (in3)
unnamed: U322.16 (B5), U325.11 (in2)
unnamed: U322.17 (B4), U325.14 (in1)
unnamed: U323.14 (B7), U325.6 (out4)
unnamed: U323.15 (B6), U325.3 (out3)
unnamed: U323.16 (B5), U325.10 (out2)
unnamed: U323.17 (B4), U325.13 (out1)
unnamed: U326.2 (in3), U327.19 (B2)
unnamed: U326.3 (out3), U328.19 (B2)
unnamed: U326.5 (in4), U327.18 (B3)
unnamed: U326.6 (out4), U328.18 (B3)
unnamed: U326.10 (out2), U328.20 (B1)
unnamed: U326.11 (in2), U327.20 (B1)
unnamed: U326.13 (out1), U328.21 (B0)
unnamed: U326.14 (in1), U327.21 (B0)
unnamed: U327.14 (B7), U329.5 (in4)
unnamed: U327.15 (B6), U329.2 (in3)
unnamed: U327.16 (B5), U329.11 (in2)
unnamed: U327.17 (B4), U329.14 (in1)
unnamed: U328.14 (B7), U329.6 (out4)
unnamed: U328.15 (B6), U329.3 (out3)
unnamed: U328.16 (B5), U329.10 (out2)
unnamed: U328.17 (B4), U329.13 (out1)
unnamed: U330.14 (B7), U332.5 (in4)
unnamed: U330.15 (B6), U332.2 (in3)
unnamed: U330.16 (B5), U332.11 (in2)
unnamed: U330.17 (B4), U332.14 (in1)
unnamed: U331.14 (B7), U332.6 (out4)
unnamed: U331.15 (B6), U332.3 (out3)
unnamed: U331.16 (B5), U332.10 (out2)
unnamed: U331.17 (B4), U332.13 (out1)

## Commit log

2024-01-06 Initial commit. The USIC design is just beginning here but I want to put the files into git and get the repository working.
2024-01-06 Initial README
2024-01-06 Moved link
